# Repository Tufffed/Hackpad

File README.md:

# Tuffed's Macropad
This has 5 MX keys with an additional Rotary Encoder, an OLED display, and RGB.

## CAD
The case it built with 4 M3 screws and 4 matching HeatPress inserts. The case consits of a bottom shell and a top lid. The PCB is held in place as it's screwed with another 3 M3 screws with the same heat press inserts to match.

<p align="center"> <strong> Made in Onshape  </strong> </p>

## PCB
<strong> Schematic </strong>
<br><br> 
<strong> PCB Layout </strong>
<br><br>
<br><p align="center"> <strong> Made in KICad  </strong> </p>

## Case 

<p align="center"> <strong> Made in Onshape  </strong> </p>

## Firmware
For this hackpad, I used QMK to controll it. At the current moment it has a single layer with copy, paste, cut, volume, and mute controlls. As I use the hakpad with more programs I will add more layers depending on my needs (the rotary encoder push switch will be used to toggle).

## Bill of Materials
| Item | Amt |
| :--- | :---: |
| PCB | 1x |
| Case (top and bottom) | 1x |
| Seed XIAO RP2040 | 1x |
| SK+912 MINI-E LED | 11x |
| EC11 Rotary Encoder | 1x |
| MX Switch | 2x |
| 1N4148 Diode | 6x |
|.91 in OLED Display | 1x |
| MX compaitble keycaps | 5x |
| M3x16mm Screw | 7x |
| M3x5mx4mm Heatpress inserts | 4x |

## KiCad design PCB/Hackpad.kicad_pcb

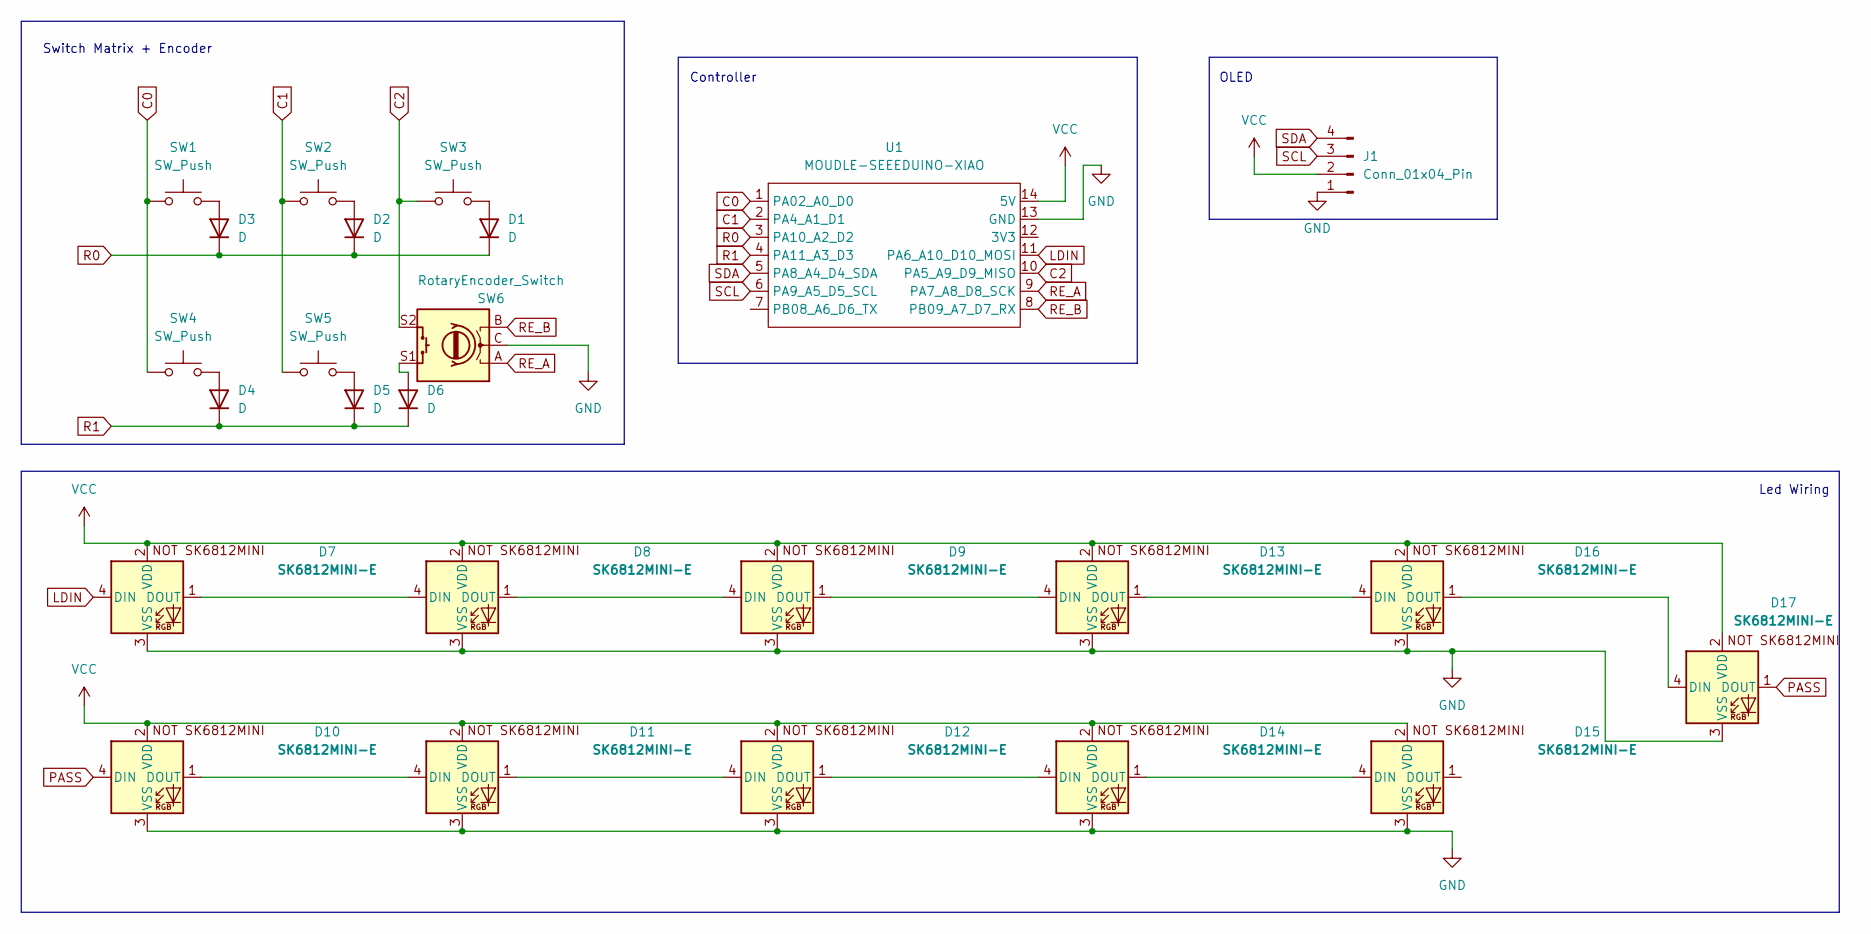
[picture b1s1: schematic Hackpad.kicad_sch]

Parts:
D1, D2, D3, D4, D5, D6: D; D_DO-35_SOD27_P7.62mm_Horizontal
D7, D8, D9, D10, D11, D12, D13, D14, D15, D16, D17: SK6812MINI-E; SK6812MINI-E_fixed
J1: Conn_01x04_Pin; SSD1306-0.91-OLED-4pin-128x32
SW1, SW2, SW3, SW4, SW5: SW_Push; SW_Cherry_MX_1.00u_PCB
SW6: RotaryEncoder_Switch; RotaryEncoder_Alps_EC11E-Switch_Vertical_H20mm
U1: MOUDLE-SEEEDUINO-XIAO; XIAO-Generic-Hybrid-14P-2.54-21X17.8MM

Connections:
C0: SW1.1, SW4.1, U1.1 (PA02_A0_D0)
C1: SW2.1, SW5.1, U1.2 (PA4_A1_D1)
C2: SW3.1, SW6.S2, U1.10 (PA5_A9_D9_MISO)
GND: D7.3 (VSS), D8.3 (VSS), D9.3 (VSS), D10.3 (VSS), D11.3 (VSS), D12.3 (VSS), D13.3 (VSS), D14.3 (VSS), D15.3 (VSS), D16.3 (VSS), D17.3 (VSS), J1.1, SW6.C, U1.13 (GND)
LDIN: D7.4 (DIN), U1.11 (PA6_A10_D10_MOSI)
unnamed: D1.2 (A), SW3.2
unnamed: D2.2 (A), SW2.2
unnamed: D3.2 (A), SW1.2
unnamed: D4.2 (A), SW4.2
unnamed: D5.2 (A), SW5.2
unnamed: D6.2 (A), SW6.S1
unnamed: D7.1 (DOUT), D8.4 (DIN)
unnamed: D8.1 (DOUT), D9.4 (DIN)
unnamed: D10.1 (DOUT), D11.4 (DIN)
unnamed: D11.1 (DOUT), D12.4 (DIN)
unnamed: D12.1 (DOUT), D14.4 (DIN)
unnamed: D9.1 (DOUT), D13.4 (DIN)
unnamed: D13.1 (DOUT), D16.4 (DIN)
unnamed: D14.1 (DOUT), D15.4 (DIN)
unnamed: D16.1 (DOUT), D17.4 (DIN)
PASS: D10.4 (DIN), D17.1 (DOUT)
R0: D1.1 (K), D2.1 (K), D3.1 (K), U1.3 (PA10_A2_D2)
R1: D4.1 (K), D5.1 (K), D6.1 (K), U1.4 (PA11_A3_D3)
RE_A: SW6.A, U1.9 (PA7_A8_D8_SCK)
RE_B: SW6.B, U1.8 (PB09_A7_D7_RX)
SCL: J1.3, U1.6 (PA9_A5_D5_SCL)
SDA: J1.4, U1.5 (PA8_A4_D4_SDA)
VCC: D7.2 (VDD), D8.2 (VDD), D9.2 (VDD), D10.2 (VDD), D11.2 (VDD), D12.2 (VDD), D13.2 (VDD), D14.2 (VDD), D15.2 (VDD), D16.2 (VDD), D17.2 (VDD), J1.2, U1.14 (5V)

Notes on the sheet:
Controller
OLED
Switch Matrix + Encoder
Led Wiring

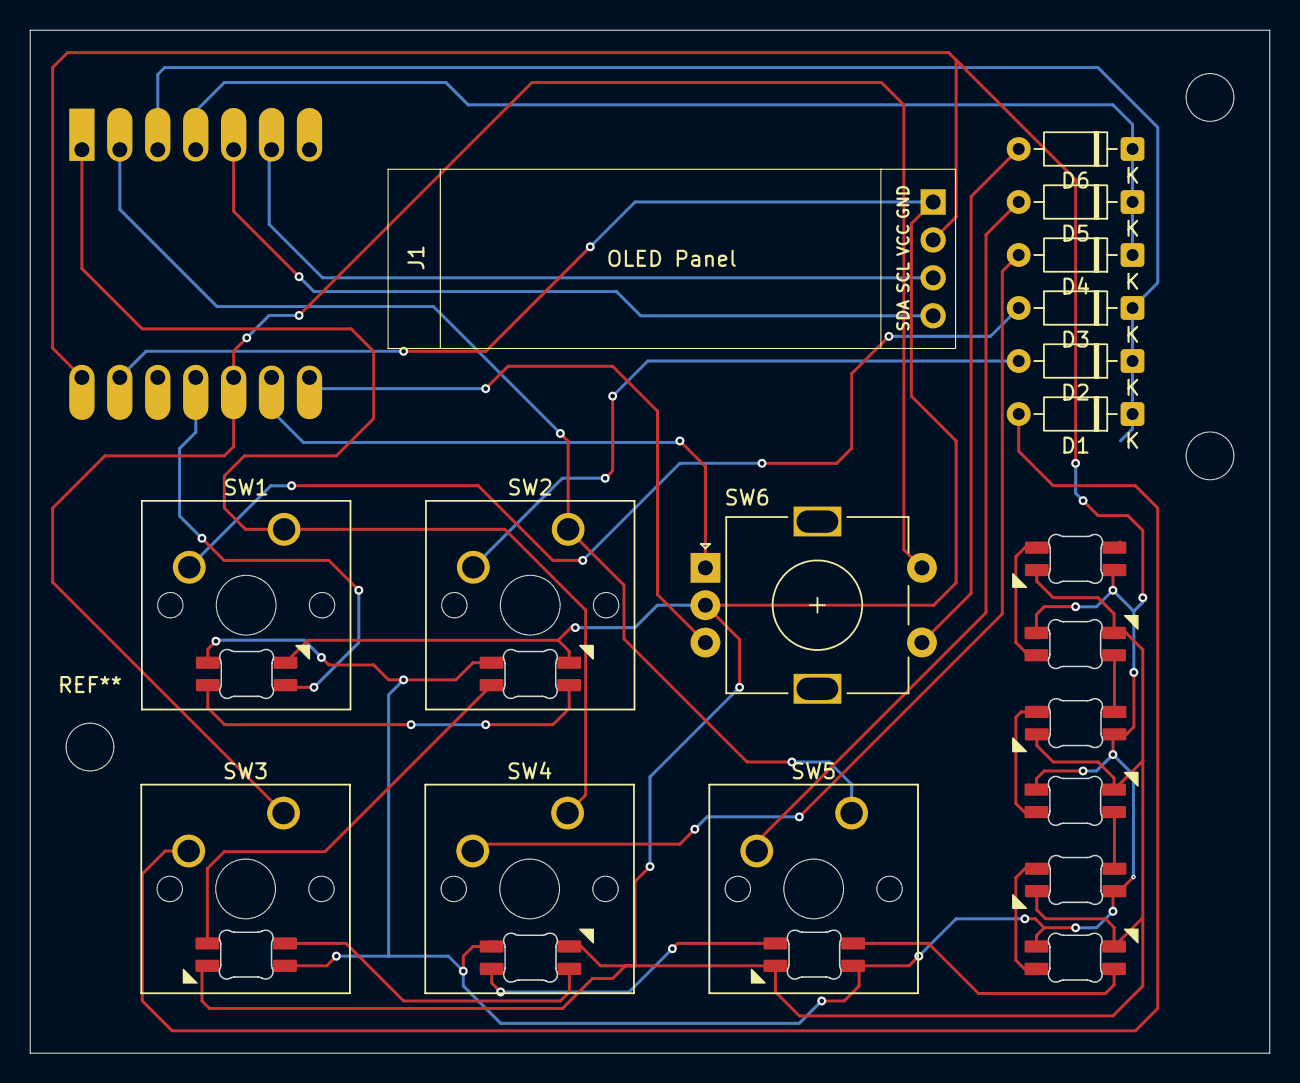
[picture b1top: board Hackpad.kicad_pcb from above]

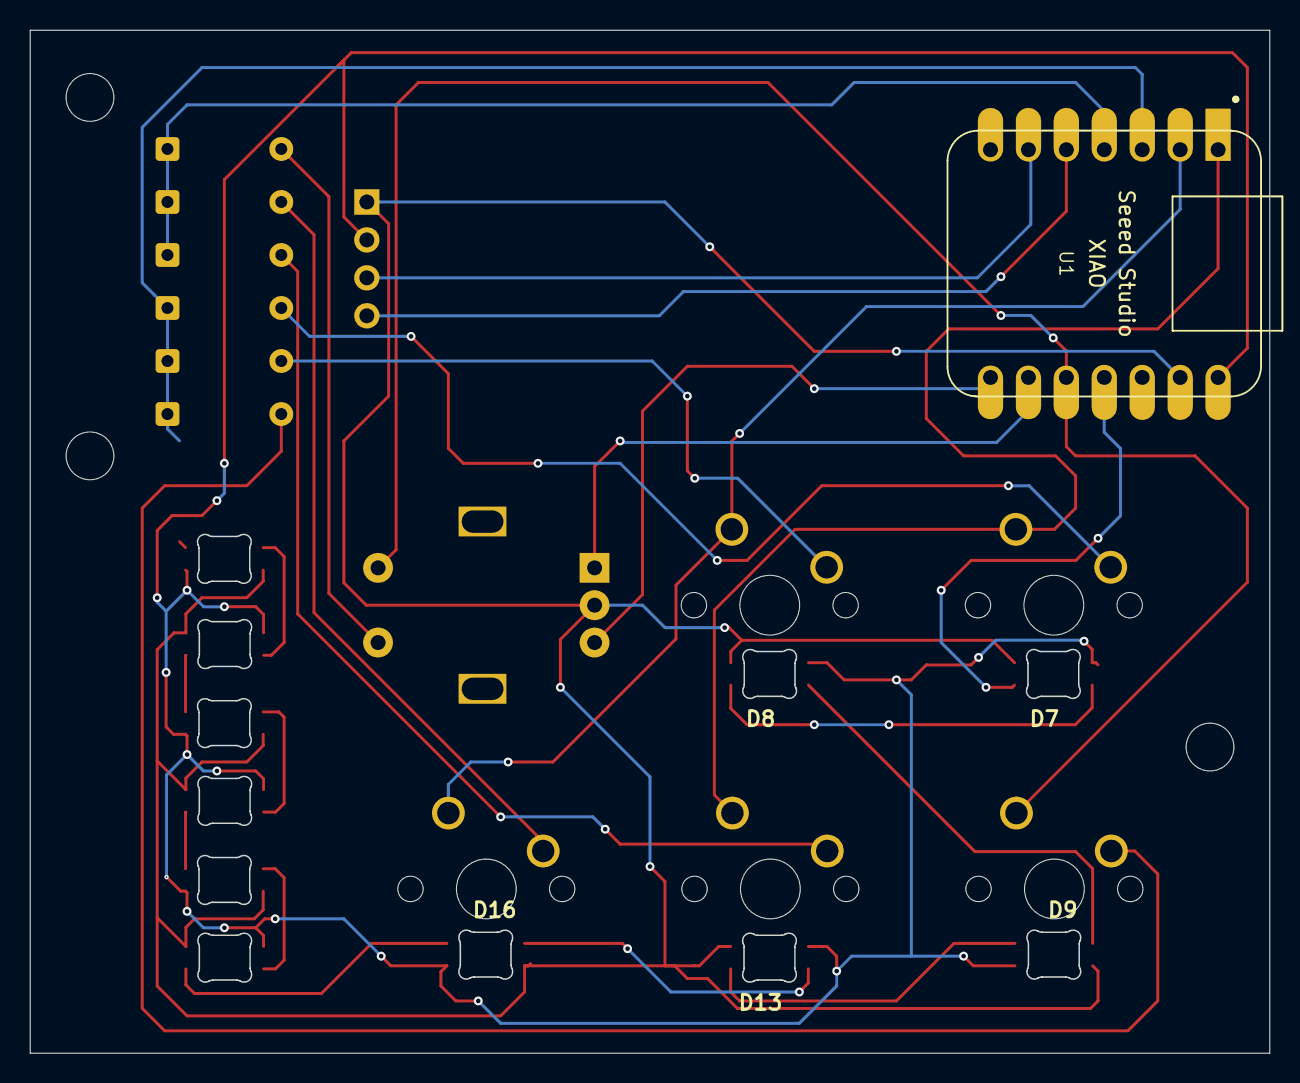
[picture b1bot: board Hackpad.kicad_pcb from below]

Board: 2 copper layers, 82.9 x 68.5 mm, 25 parts (12 on the bottom side), 28 nets.

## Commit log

2026-05-20 qmk Code
    working I think? I don't have hardware to test yet.
2026-05-25 Rename
2026-05-25 Added PCB
2026-05-25 Added production and PCB
2026-05-25 Added 3d Print Files
2026-05-25 updated 3d print names
